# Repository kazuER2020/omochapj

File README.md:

# omochapj
KiCad_data for omochaPJ(dflamingo).

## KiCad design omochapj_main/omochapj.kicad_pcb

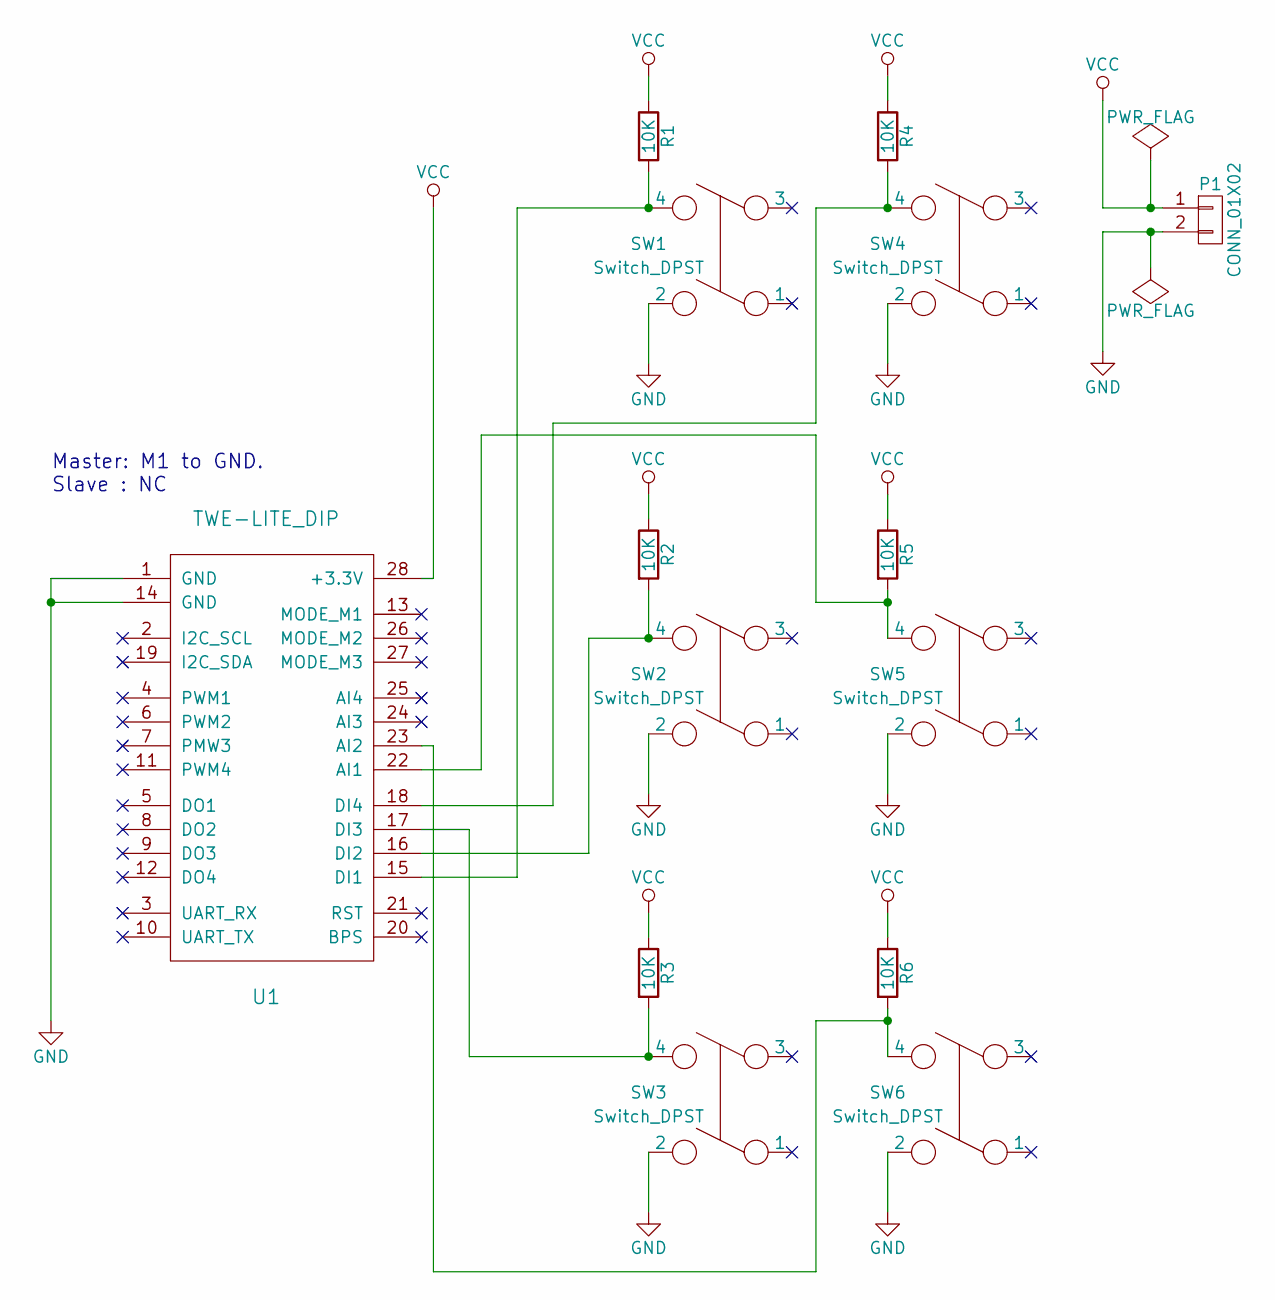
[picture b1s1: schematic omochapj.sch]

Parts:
P1: CONN_01X02; XH_conn2
R1, R2, R3, R4, R5, R6: 10K; R_Resistor_Horizontal_RM10mm
SW1, SW2, SW3, SW4, SW5, SW6: Switch_DPST; SW_Tactile_6x6mm
U1: TWE-LITE_DIP

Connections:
GND: P1.2, SW1.2, SW2.2, SW3.2, SW4.2, SW5.2, SW6.2, U1.1 (GND), U1.14 (GND)
unnamed: R1.2, SW1.4, U1.15 (DI1)
unnamed: R2.2, SW2.4, U1.16 (DI2)
unnamed: R3.2, SW3.4, U1.17 (DI3)
unnamed: R4.2, SW4.4, U1.18 (DI4)
unnamed: R5.2, SW5.4, U1.22 (AI1)
unnamed: R6.2, SW6.4, U1.23 (AI2)
VCC: P1.1, R1.1, R2.1, R3.1, R4.1, R5.1, R6.1, U1.28 (+3.3V)

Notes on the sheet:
Master: M1 to GND. Slave : NC

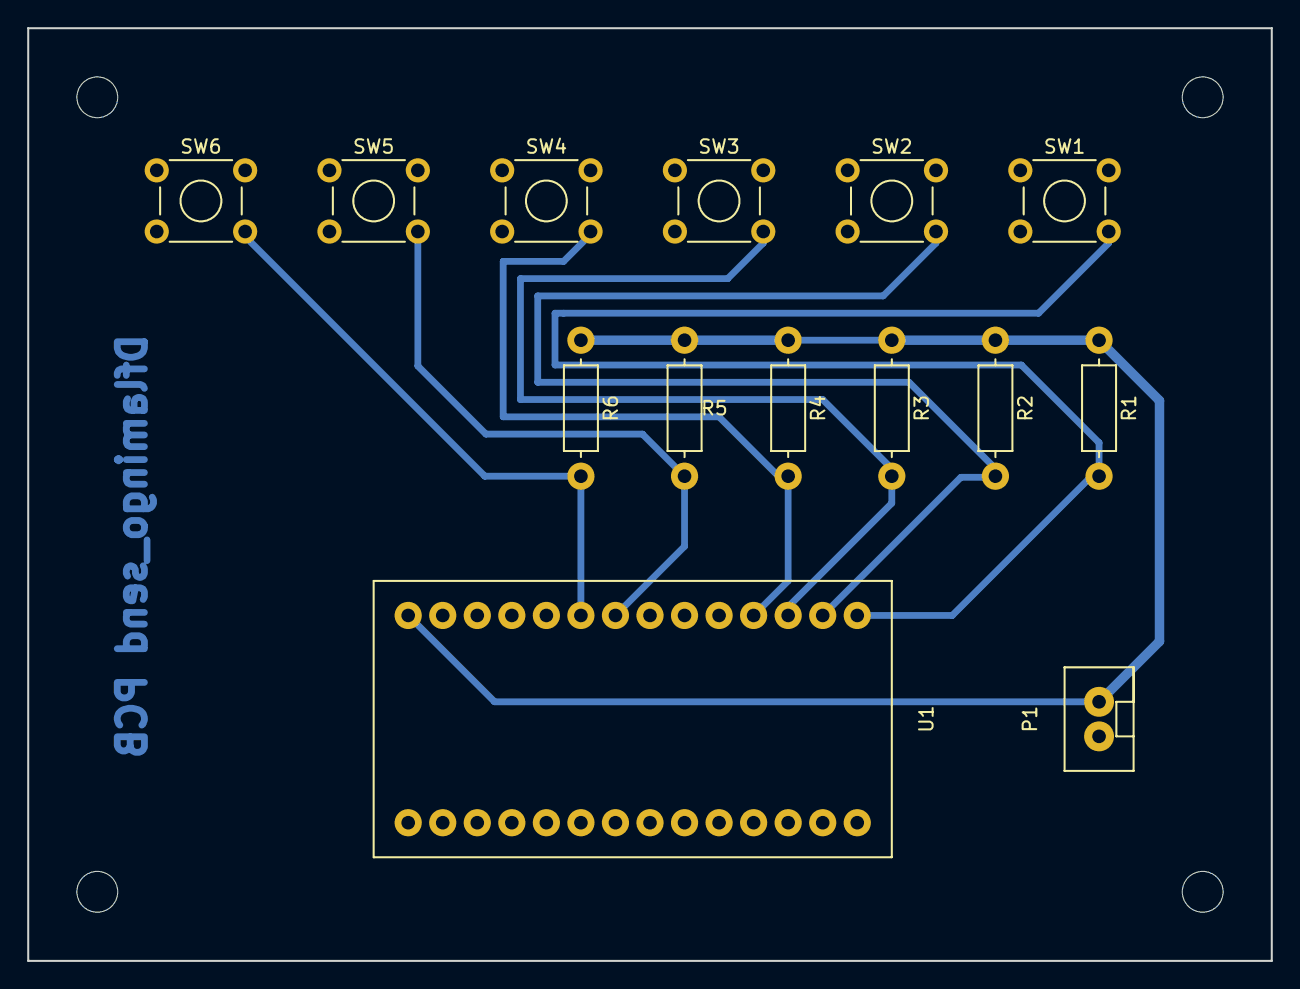
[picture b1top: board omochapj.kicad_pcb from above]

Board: 2 copper layers, 91.4 x 68.6 mm, 14 parts (0 on the bottom side), 8 nets.
